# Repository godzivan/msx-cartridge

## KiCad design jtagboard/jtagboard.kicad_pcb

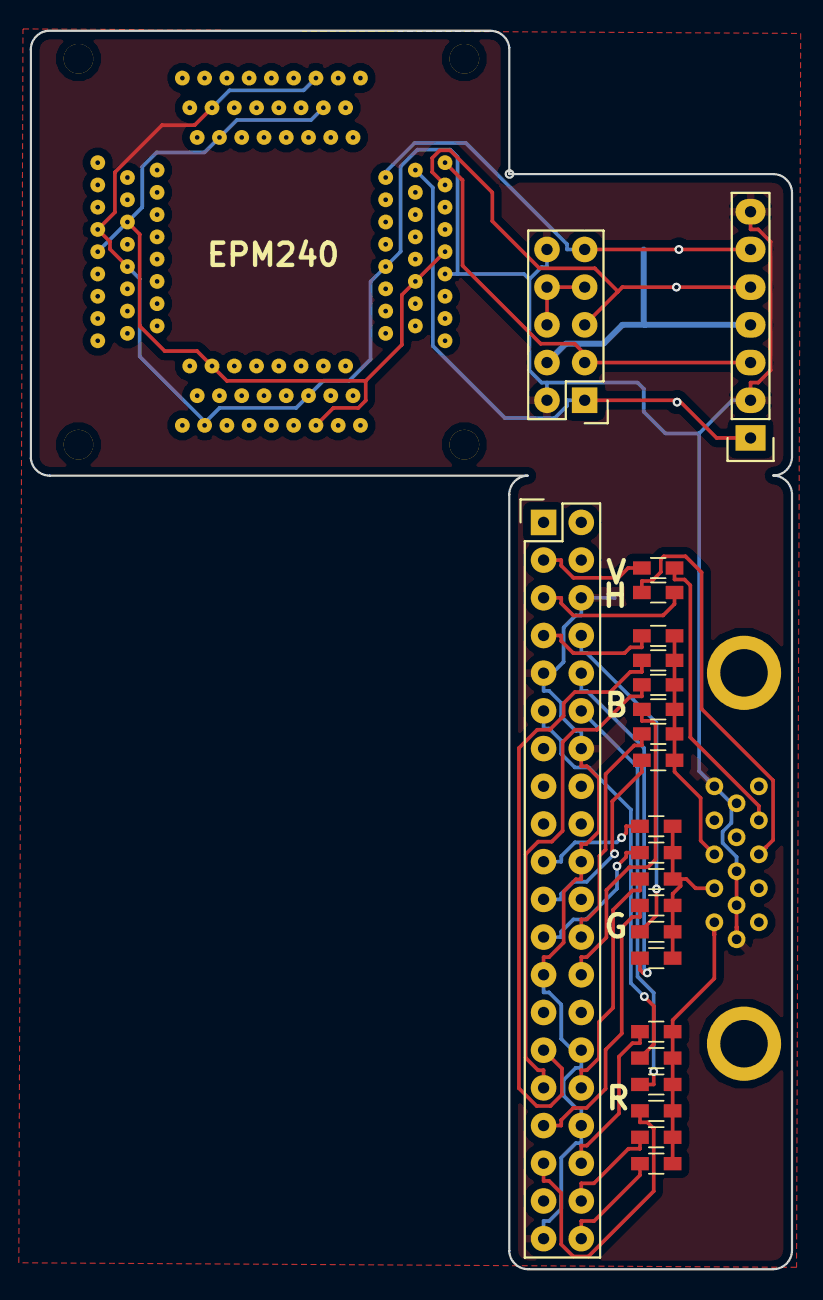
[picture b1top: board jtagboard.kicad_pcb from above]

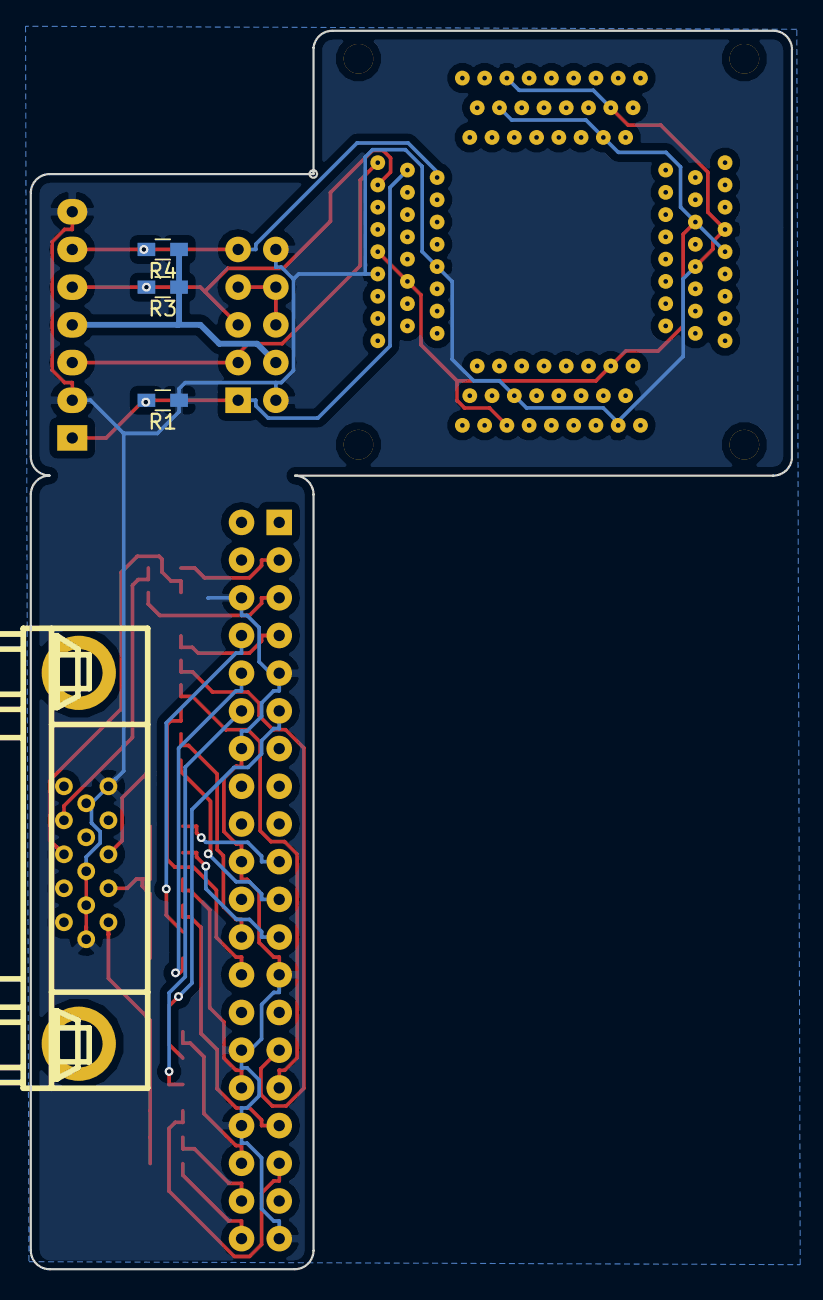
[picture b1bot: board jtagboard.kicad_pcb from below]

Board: 2 copper layers, 51.3 x 83.4 mm, 28 parts (4 on the bottom side), 33 nets.

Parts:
J1: Conn_02x05_Odd_Even; Pin_Header_Straight_2x05
J2: Conn_01x07_Male; Pin_Header_Straight_1x07
J3: DB15_Female_HighDensity; DB_15F-VGA
J4: Raspberry_Pi_2_3; Pin_Header_Straight_2x20
R1, R3, R4, R5, R6, R7, R8, R9, R10, R11, R12, R13, R14, R15, R16, R17, R18, R19, R20, R21, R22, R23, R24: R; R_0603_HandSoldering
U1: MaxII_EPM240; tqfp100

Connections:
/3V3: U1.9, U1.13, U1.31, U1.45, U1.59, U1.63, U1.80, U1.94
/B2: J4.7, R5.2
/B3: J4.29, R6.2
/B4: J4.31, R7.2
/B5: J4.26, R8.2
/B6: J4.24, R9.2
/B7: J4.21, R10.2
/Blue: J3.3, R5.1, R6.1, R7.1, R8.1, R9.1, R10.1
/G2: J4.19, R17.2
/G3: J4.23, R18.2
/G4: J4.32, R19.2
/G5: J4.33, R20.2
/G6: J4.8, R21.2
/G7: J4.10, R22.2
/GND: J1.2, J1.10, J2.2, J2.7, J3.5, J3.6, J3.7, J3.8, J3.10, J4.6, J4.9, J4.14, J4.20, J4.25, J4.30, J4.34, J4.39, R1.1, U1.10, U1.11, U1.32, U1.46, U1.60, U1.65, U1.79, U1.93
/Green: J3.2, R17.1, R18.1, R19.1, R20.1, R21.1, R22.1
/HSync: J3.13, R24.1
/NC: J1.6, J1.7, J1.8
/R2: J4.36, R11.2
/R3: J4.11, R12.2
/R4: J4.12, R13.2
/R5: J4.35, R14.2
/R6: J4.38, R15.2
/R7: J4.40, R16.2
/Red: J3.1, R11.1, R12.1, R13.1, R14.1, R15.1, R16.1
/TCK: J1.1, J2.1, R1.2, U1.24
/TDI: J1.9, J2.6, R4.2, U1.23
/TDO: J1.3, J2.3, U1.25
/TMS: J1.5, J2.5, R3.2, U1.22
/VCC(TRGT): J1.4, J2.4, R3.1, R4.1
/VSync: J3.14, R23.1
/piHSYNC: J4.5, R24.2
/piVSYNC: J4.3, R23.2

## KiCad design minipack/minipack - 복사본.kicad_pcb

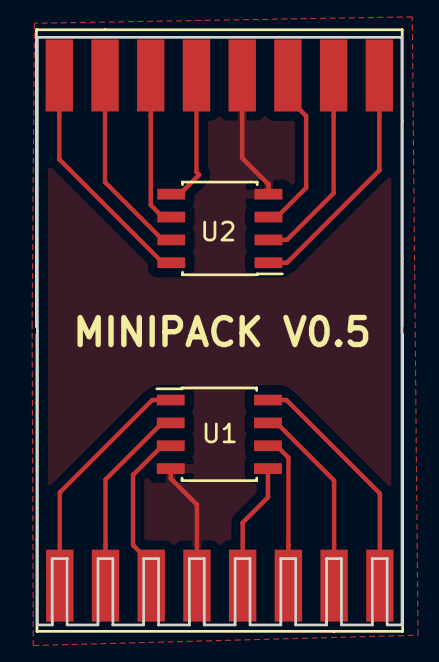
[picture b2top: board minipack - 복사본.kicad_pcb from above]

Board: 2 copper layers, 20.3 x 32.6 mm, 4 parts (0 on the bottom side), 15 nets.

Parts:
J1, J2: Conn_01x08; minipack
U1, U2: W25Q16BVSSIG; SOIC-8_3.9x4.9mm_Pitch1.27mm

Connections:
/CLK: J1.6, U1.6
/CLK2: J2.6, U2.6
/CS: J1.1, U1.1
/CS2: J2.1, U2.1
/GND: J1.4, J2.4, U1.4, U2.4
/HOLD: J1.7, U1.7
/HOLD2: J2.7, U2.7
/MISO: J1.2, U1.2
/MISO2: J2.2, U2.2
/MOSI: J1.5, U1.5
/MOSI2: J2.5, U2.5
/VCC: J1.8, U1.8
/VCC2: J2.8, U2.8
/WP: J1.3, U1.3
/WP2: J2.3, U2.3

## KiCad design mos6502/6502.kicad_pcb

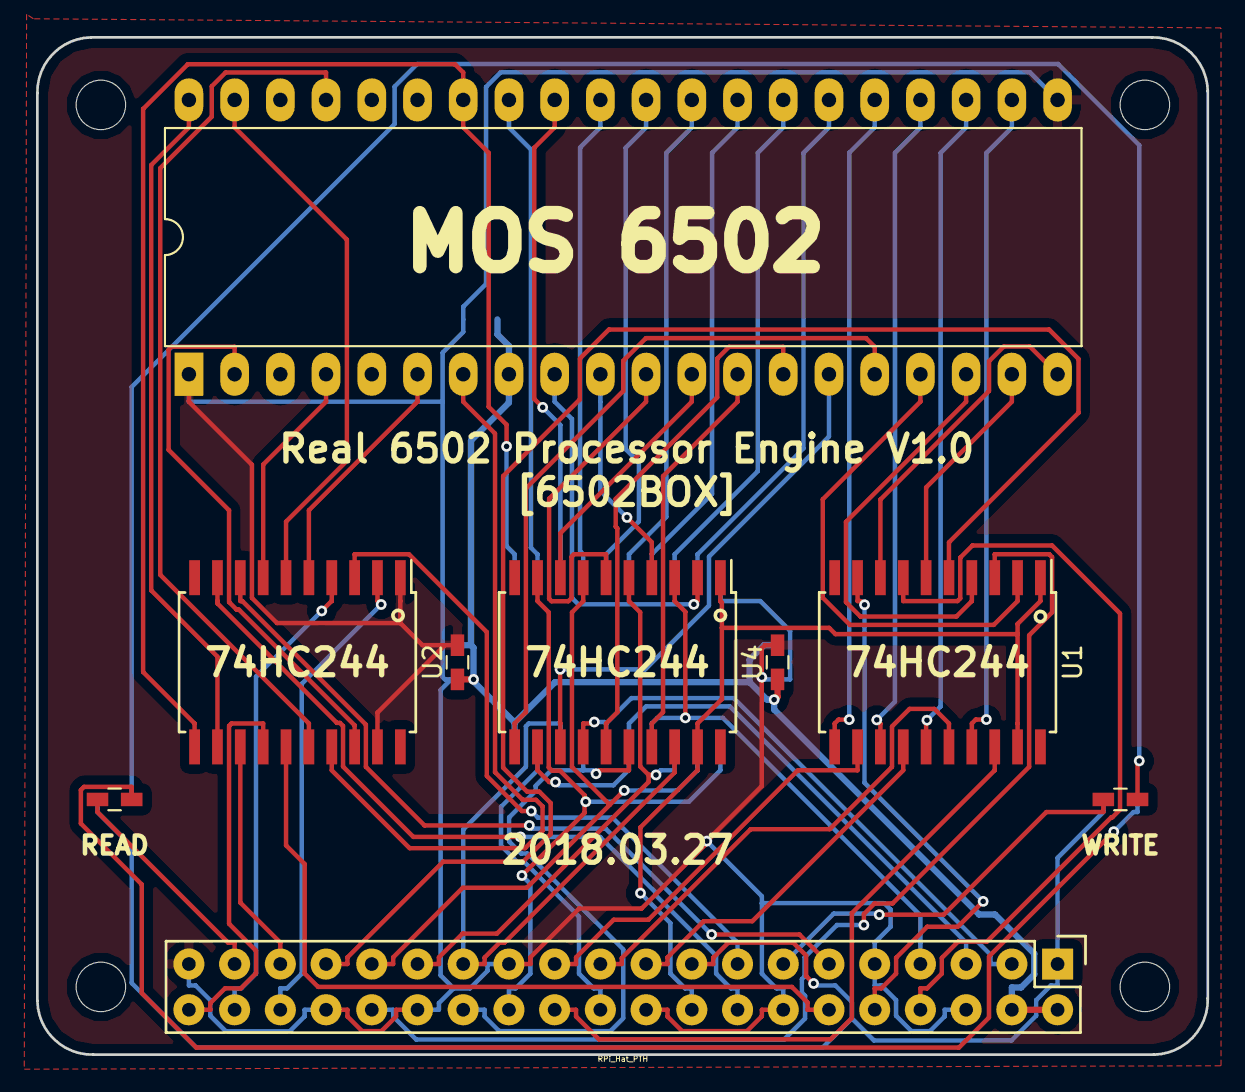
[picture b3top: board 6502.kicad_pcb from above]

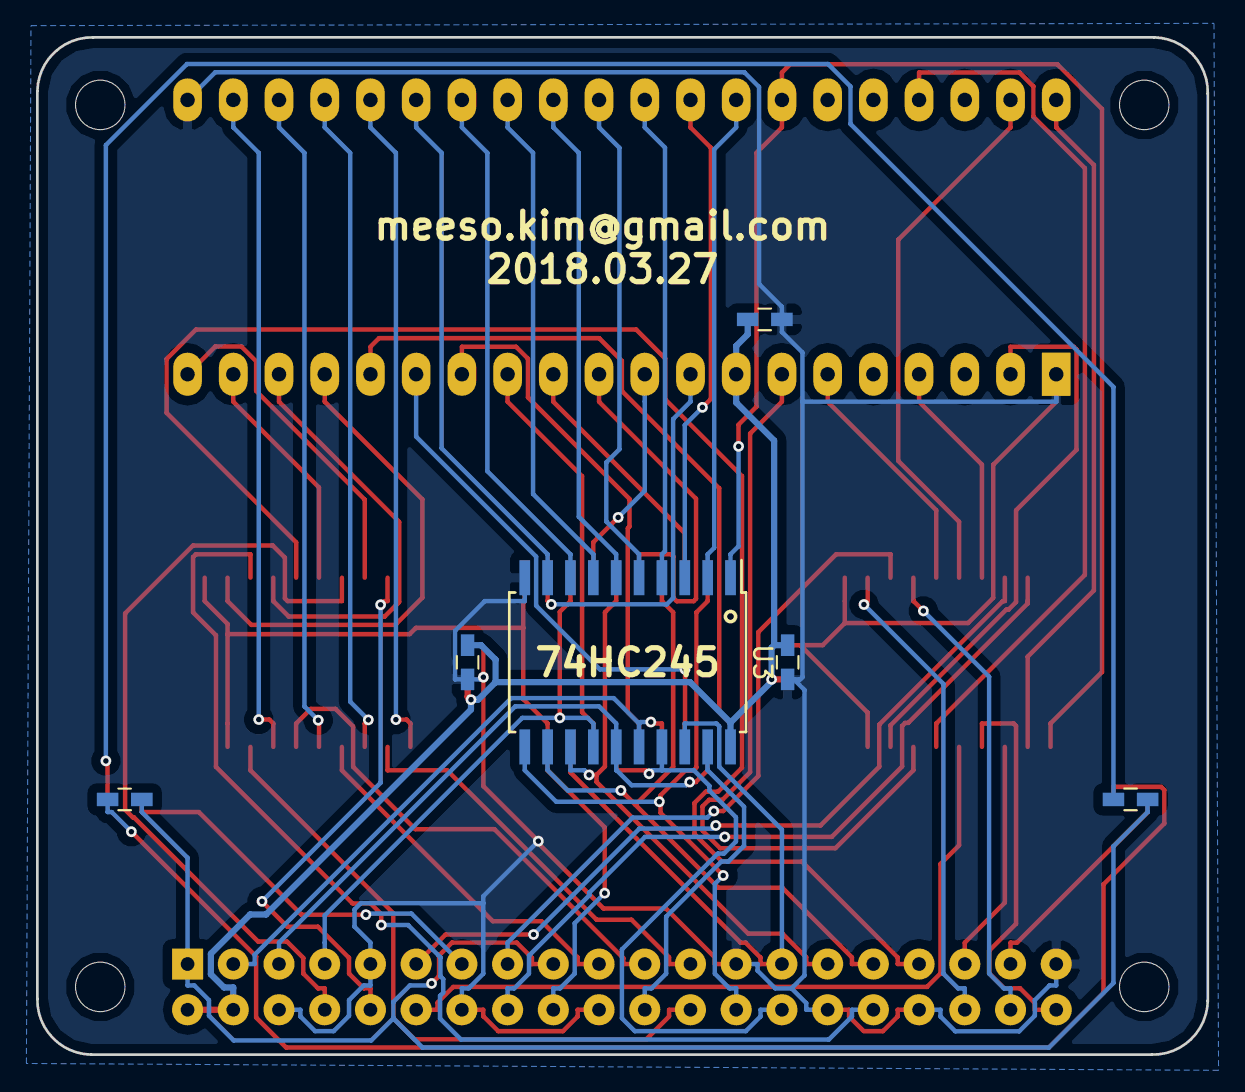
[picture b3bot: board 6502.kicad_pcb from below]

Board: 2 copper layers, 65.0 x 56.5 mm, 15 parts (6 on the bottom side), 65 nets.

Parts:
C1, C2, C3, C4, C5: C; C_0603_HandSoldering
D1, D2: LED; C_0603_HandSoldering
J1: Raspberry_Pi_2_3; Pin_Header_Straight_2x20
R1, R2: R; C_0603_HandSoldering
U1, U2, U4: 74HC244; SOIC-20W_7.5x12.8mm_Pitch1.27mm
U3: 74HC245; SOIC-20W_7.5x12.8mm_Pitch1.27mm
U5: WD65C02; DIP-40_W15.24mm_LongPads

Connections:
/3V3: J1.1, J1.17, R1.1, R2.1
/A0: U4.2, U5.9
/A1: U4.4, U5.10
/A2: U4.6, U5.11
/A3: U4.8, U5.12
/A4: U4.17, U5.13
/A5: U4.15, U5.14
/A6: U4.13, U5.15
/A7: U4.11, U5.16
/A8: U1.2, U5.17
/A9: U1.4, U5.18
/A10: U1.6, U5.19
/A11: U1.8, U5.20
/A12: U1.17, U5.22
/A13: U1.15, U5.23
/A14: U1.13, U5.24
/A15: U1.11, U5.25
/D0: U3.2, U5.33
/D1: U3.3, U5.32
/D2: U3.4, U5.31
/D3: U3.5, U5.30
/D4: U3.6, U5.29
/D5: U3.7, U5.28
/D6: U3.8, U5.27
/D7: U3.9, U5.26
/IRQ: U2.7, U5.4
/NMI: U2.5, U5.6
/PHI0: U2.16, U5.37
/PHI2o: U2.6, U5.39
/RA8: J1.24, U1.18
/RA9: J1.21, U1.16
/RA10: J1.19, U1.14
/RA11: J1.23, U1.12
/RA12: J1.32, U1.3
/RA13: J1.33, U1.5
/RA14: J1.8, U1.7
/RA15: J1.10, U1.9
/RC16: J1.36, U2.2
/RC17: J1.11, U2.8
/RC18: J1.12, U2.15
/RC19: J1.35, U2.13
/RC20: J1.38, U2.4
/RC21: J1.40, U2.14
/RC22: J1.15, U2.3
/RC23: J1.16, U2.9
/RC24: J1.18, U1.1, U1.19, U4.1, U4.19
/RC25: J1.22, U3.19
/RC26: D1.1, J1.37
/RC27: D2.1, J1.13
/RD0: J1.27, U3.18, U4.18
/RD1: J1.28, U3.17, U4.16
/RD2: J1.3, U3.16, U4.14
/RD3: J1.5, U3.15, U4.12
/RD4: J1.7, U3.14, U4.3
/RD5: J1.29, U3.13, U4.5
/RD6: J1.31, U3.12, U4.7
/RD7: J1.26, U3.11, U4.9
/RDY: U2.18, U5.2
/RESET: U2.12, U5.40
/RW: U2.11, U3.1, U5.34
/SYNC: U2.17, U5.7
GND: C1.2, C2.2, C3.2, C4.2, C5.2, J1.6, J1.9, J1.14, J1.20, J1.25, J1.30, J1.34, J1.39, U2.1, U2.19, U3.10, U5.1, U5.21
unnamed: D1.2, R1.2
unnamed: D2.2, R2.2
VCC: C1.1, C2.1, C3.1, C4.1, C5.1, J1.2, J1.4, U3.20, U5.8

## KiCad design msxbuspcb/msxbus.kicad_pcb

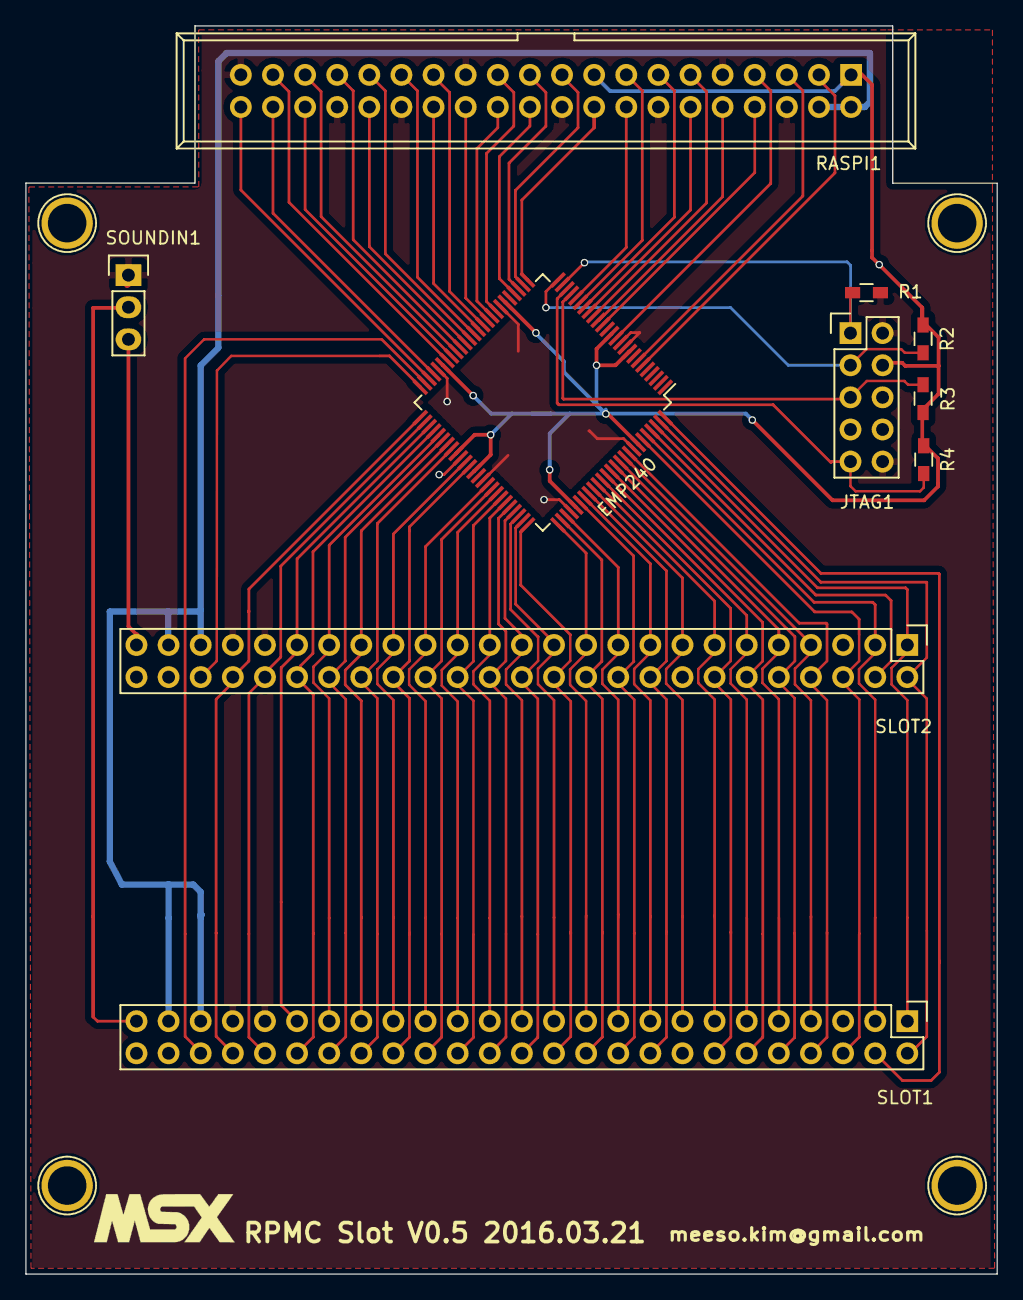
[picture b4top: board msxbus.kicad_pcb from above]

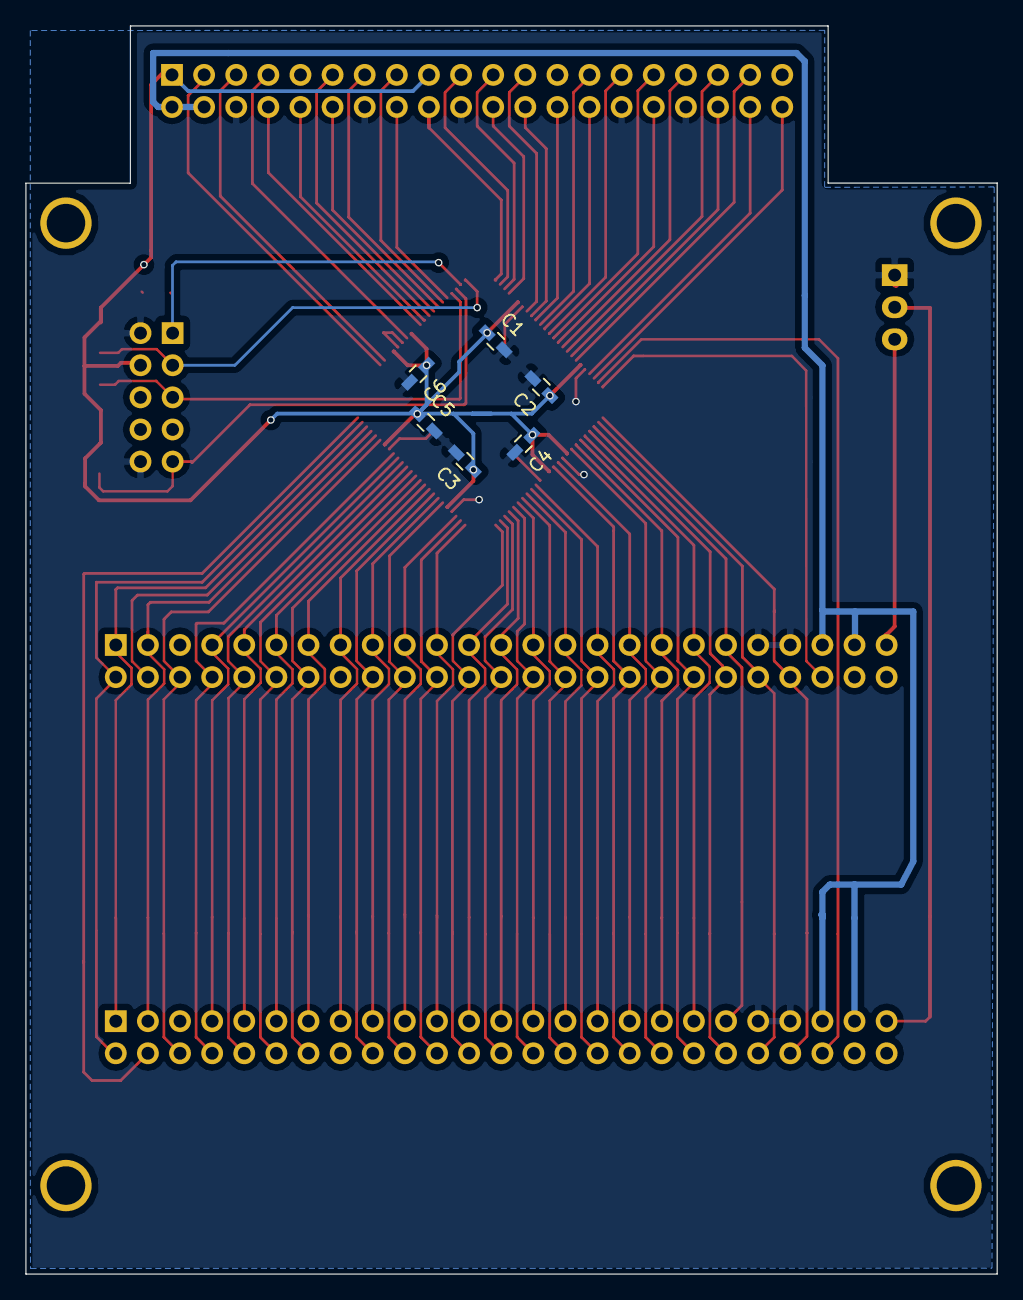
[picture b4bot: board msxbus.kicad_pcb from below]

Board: 2 copper layers, 76.8 x 98.7 mm, 16 parts (6 on the bottom side), 80 nets.

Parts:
C1, C2, C3, C4, C5, C6: C; C_0603_HandSoldering
EMP240: EMP240; TQFP-100_14x14mm_Pitch0.5mm
JTAG1: CONN_02X05; Pin_Header_Straight_2x05
R1, R2, R3, R4: 10K; R_0603_HandSoldering
RASPI1: RPi_GPIO; IDC_Header_Straight_40pins
SLOT1, SLOT2: CONN_02X25; Pin_Header_Straight_2x25
SOUNDIN1: CONN_01X03; Pin_Header_Straight_1x03

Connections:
+3V3: C1.1, C2.1, C3.1, C4.1, C5.1, C6.1, EMP240.9, EMP240.13, EMP240.31, EMP240.45, EMP240.59, EMP240.63, EMP240.80, EMP240.94, JTAG1.4, R2.1, R3.1, R4.1, RASPI1.1, RASPI1.17
+5V: RASPI1.2, RASPI1.4, SLOT1.45, SLOT1.47, SLOT2.45, SLOT2.47
/A0: EMP240.71, SLOT1.28, SLOT2.28
/A1: EMP240.70, SLOT1.27, SLOT2.27
/A2: EMP240.69, SLOT1.30, SLOT2.30
/A3: EMP240.68, SLOT1.29, SLOT2.29
/A4: EMP240.67, SLOT1.32, SLOT2.32
/A5: EMP240.66, SLOT1.31, SLOT2.31
/A6: EMP240.77, SLOT1.22, SLOT2.22
/A7: EMP240.76, SLOT1.21, SLOT2.21
/A8: EMP240.75, SLOT1.24, SLOT2.24
/A9: EMP240.82, SLOT1.17, SLOT2.17
/A10: EMP240.81, SLOT1.20, SLOT2.20
/A11: EMP240.78, SLOT1.19, SLOT2.19
/A12: EMP240.74, SLOT1.23, SLOT2.23
/A13: EMP240.73, SLOT1.26, SLOT2.26
/A14: EMP240.72, SLOT1.25, SLOT2.25
/A15: EMP240.83, SLOT1.18, SLOT2.18
/BUSDIR: EMP240.90, SLOT1.10, SLOT2.10
/CLOCK: EMP240.52, SLOT1.42, SLOT2.42
/CS1: EMP240.98, SLOT1.1, SLOT2.1
/CS2: EMP240.99, SLOT1.2, SLOT2.2
/CS12: EMP240.96, SLOT1.3, SLOT2.3
/D0: EMP240.62, SLOT1.34, SLOT2.34
/D1: EMP240.61, SLOT1.33, SLOT2.33
/D2: EMP240.58, SLOT1.36, SLOT2.36
/D3: EMP240.57, SLOT1.35, SLOT2.35
/D4: EMP240.56, SLOT1.38, SLOT2.38
/D5: EMP240.55, SLOT1.37, SLOT2.37
/D6: EMP240.54, SLOT1.40, SLOT2.40
/D7: EMP240.53, SLOT1.39, SLOT2.39
/INT: EMP240.92, SLOT1.8, SLOT2.8
/IORQ: EMP240.87, SLOT1.11, SLOT2.11
/M1: EMP240.89, SLOT1.9, SLOT2.9
/MA0: EMP240.26, RASPI1.18
/MCS: EMP240.44, RASPI1.37
/MD00: EMP240.36, RASPI1.27
/MD01: EMP240.37, RASPI1.28
/MD02: EMP240.6, RASPI1.3
/MD03: EMP240.7, RASPI1.5
/MD04: EMP240.12, RASPI1.7
/MD05: EMP240.38, RASPI1.29
/MD06: EMP240.39, RASPI1.31
/MD07: EMP240.35, RASPI1.26
/MD08: EMP240.34, RASPI1.24
/MD09: EMP240.28, RASPI1.21
/MD10: EMP240.27, RASPI1.19
/MD11: EMP240.33, RASPI1.23
/MD12: EMP240.40, RASPI1.32
/MD13: EMP240.41, RASPI1.33
/MD14: EMP240.15, RASPI1.8
/MD15: EMP240.16, RASPI1.10
/MERQ: EMP240.88, SLOT1.12, SLOT2.12
/MEXT: EMP240.19, RASPI1.13
/MIORQ: EMP240.42, RASPI1.35
/MMERQ: EMP240.18, RASPI1.12
/MODE: EMP240.29, RASPI1.22
/MRD: EMP240.17, RASPI1.11
/MRESET: EMP240.47, RASPI1.38
/MSLTSL0: EMP240.48, RASPI1.40
/MSLTSL1: EMP240.20, RASPI1.15
/MWAIT: EMP240.21, RASPI1.16
/MWR: EMP240.43, RASPI1.36
/NWAIT: EMP240.91, SLOT1.7, SLOT2.7
/RD: EMP240.86, SLOT1.14, SLOT2.14
/RESET: EMP240.84, SLOT1.15, SLOT2.15
/RFSH: EMP240.95, SLOT1.6, SLOT2.6
/SLTSL0: EMP240.97, SLOT2.4
/SLTSL1: EMP240.100, SLOT1.4
/SOUNDIN0: SLOT1.49, SOUNDIN1.2
/SOUNDIN1: SLOT2.49, SOUNDIN1.3
/SW1: EMP240.50, SLOT2.46
/SW2: EMP240.49, SLOT1.46
/SWOUT: EMP240.51, SLOT1.44, SLOT2.44
/TCK: EMP240.24, JTAG1.1, R1.2
/TDI: EMP240.23, JTAG1.9, R4.2
/TDO: EMP240.25, JTAG1.3, R2.2
/TMS: EMP240.22, JTAG1.5, R3.2
/WR: EMP240.85, SLOT1.13, SLOT2.13
GND: C1.2, C2.2, C3.2, C4.2, C5.2, C6.2, EMP240.10, EMP240.11, EMP240.32, EMP240.46, EMP240.60, EMP240.65, EMP240.79, EMP240.93, JTAG1.2, JTAG1.10, R1.1, RASPI1.6, RASPI1.9, RASPI1.14, RASPI1.20, RASPI1.25, RASPI1.30, RASPI1.34, RASPI1.39, SLOT1.41, SLOT1.43, SLOT2.41, SLOT2.43, SOUNDIN1.1

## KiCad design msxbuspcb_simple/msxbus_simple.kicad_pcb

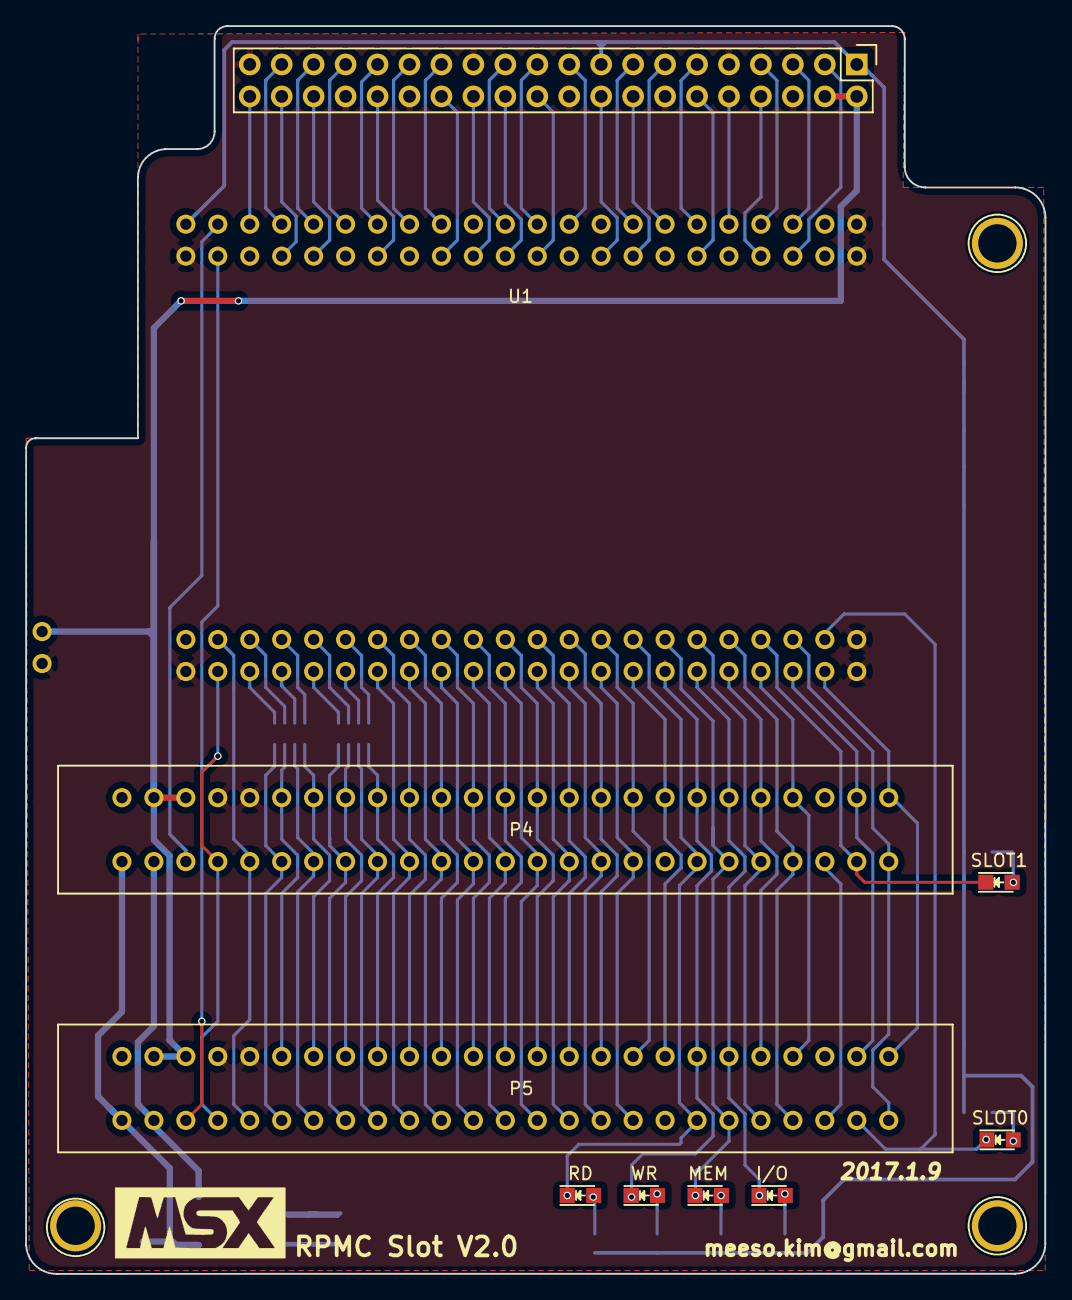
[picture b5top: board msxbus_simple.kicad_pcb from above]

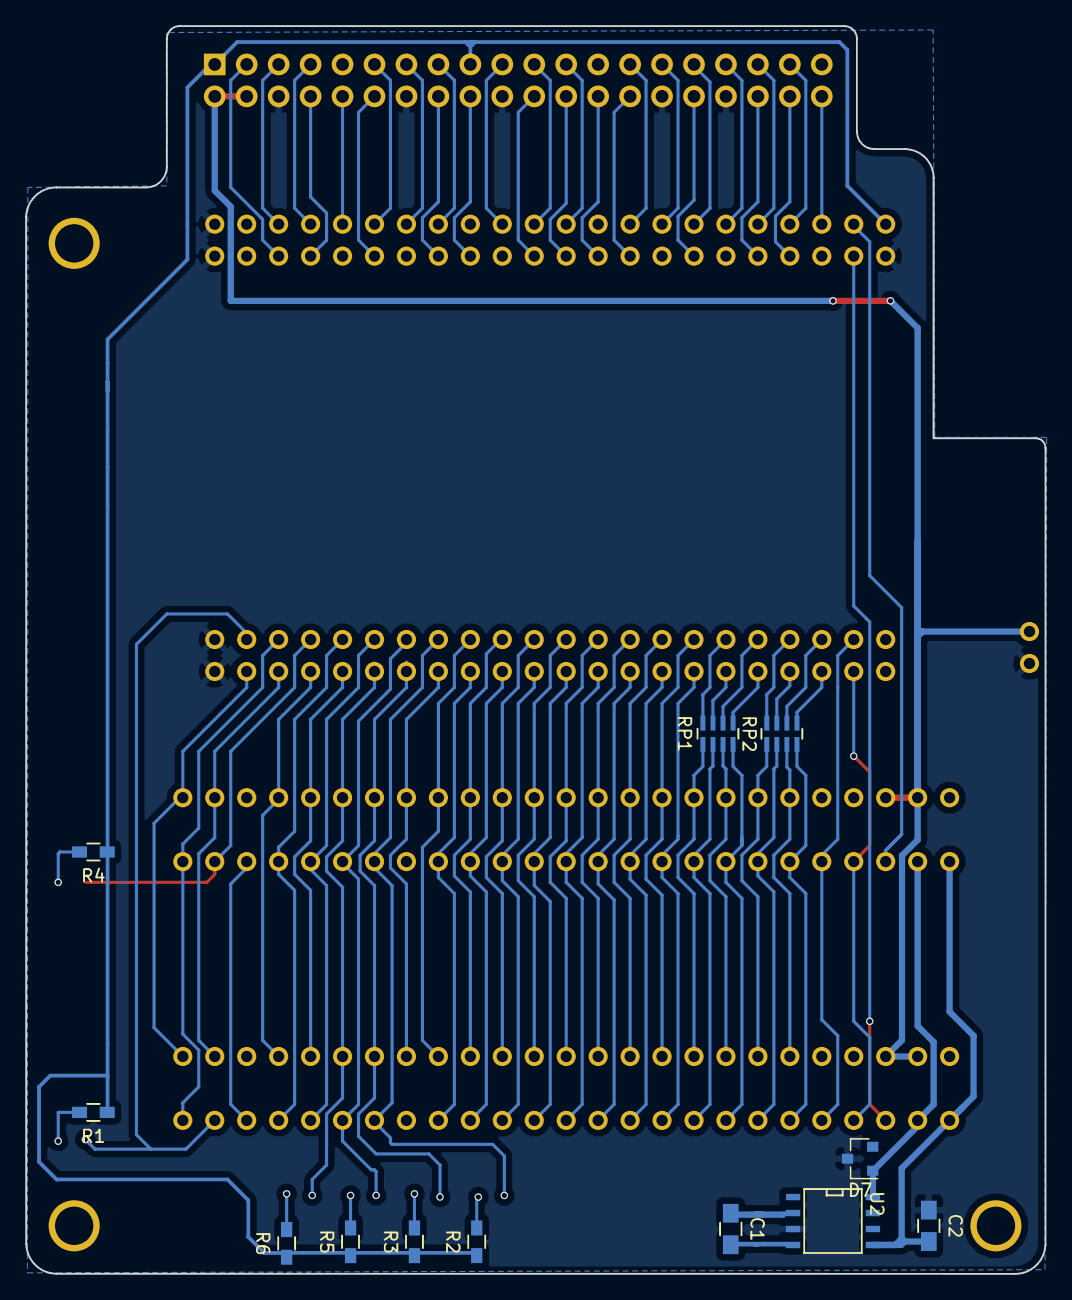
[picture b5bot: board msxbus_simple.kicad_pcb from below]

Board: 2 copper layers, 81.0 x 99.2 mm, 22 parts (12 on the bottom side), 92 nets.

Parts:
C1, C2: CP1; C_0805_HandSoldering
D7: D_Schottky_x2_Serial_AKC; SOT-23
I/O: LED; LED_0805
J1: RPi_GPIO; Pin_Header_Straight_2x20
MEM: LED; LED_0805
P4, P5: CONN_02X25; MSX_SLOT
R1, R2, R3, R4, R5, R6: R; R_0603_HandSoldering
RD: LED; LED_0805
RP1, RP2: R_PACK4; R_Array_Concave_4x0603
SLOT0, SLOT1: LED; LED_0805
U1: CPLD; emp270_board
U2: ICL7660A; SOIC-8-N
WR: LED; LED_0805

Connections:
+3V3: J1.1, J1.17, R1.1, R2.1, R3.1, R4.1, R5.1, R6.1, U1.43, U1.46
+5V: J1.2, J1.4, P4.45, P4.47, P5.45, P5.47, U1.89
+12V: D7.1, P4.48, P5.48, U2.8
/-12V: C2.2, P4.50, P5.50, U2.5
/A0: P4.28, P5.28, U1.61
/A1: P4.27, P5.27, U1.62
/A2: P4.30, P5.30, U1.59
/A3: P4.29, P5.29, U1.60
/A4: P4.32, P5.32, U1.57
/A5: P4.31, P5.31, U1.58
/A6: P4.22, P5.22, U1.67
/A7: P4.21, P5.21, U1.68
/A8: P4.24, P5.24, U1.65
/A9: P4.17, P5.17, U1.72
/A10: P4.20, P5.20, U1.69
/A11: P4.19, P5.19, U1.70
/A12: P4.23, P5.23, U1.66
/A13: P4.26, P5.26, U1.63
/A14: P4.25, P5.25, U1.64
/A15: P4.18, P5.18, U1.71
/BUSDIR: P4.10, P5.10, U1.78
/C+: C1.1, U2.2
/C-: C1.2, U2.4
/CLOCK: P4.42, P5.42, U1.48
/CS1: P4.1, P5.1, U1.85
/CS2: P4.2, P5.2, U1.84
/CS12: P4.3, P5.3, U1.83
/D0: P4.34, P5.34, RP1.2
/D1: P4.33, P5.33, RP1.1
/D2: P4.36, P5.36, RP1.4
/D3: P4.35, P5.35, RP1.3
/D4: P4.38, P5.38, RP2.2
/D5: P4.37, P5.37, RP2.1
/D6: P4.40, P5.40, RP2.4
/D7: P4.39, P5.39, RP2.3
/INT: P4.8, P5.8, U1.80
/IORQ: I/O.1, P4.11, P5.11, U1.77
/M1: P4.9, P5.9, U1.79
/MA0: J1.18, U1.18
/MCS: J1.37, U1.37
/MD00: J1.27, U1.27
/MD01: J1.28, U1.28
/MD02: J1.3, U1.6
/MD03: J1.5, U1.5
/MD04: J1.7, U1.7
/MD05: J1.29, U1.29
/MD06: J1.31, U1.31
/MD07: J1.26, U1.26
/MD08: J1.24, U1.24
/MD09: J1.21, U1.21
/MD10: J1.19, U1.19
/MD11: J1.23, U1.23
/MD12: J1.32, U1.32
/MD13: J1.33, U1.33
/MD14: J1.8, U1.8
/MD15: J1.10, U1.9
/MERQ: MEM.1, P4.12, P5.12, U1.76
/MEXT: J1.13, U1.13
/MIORQ: J1.35, U1.35
/MMERQ: J1.12, U1.12
/MODE: J1.22, U1.22
/MRD: J1.11, U1.11
/MRESET: J1.38, U1.38
/MSLTSL0: J1.40, U1.39
/MSLTSL1: J1.15, U1.15
/MWAIT: J1.16, U1.16
/MWR: J1.36, U1.36
/NWAIT: P4.7, P5.7, U1.81
/RD: P4.14, P5.14, RD.1, U1.74
/RD0: RP1.7, U1.55
/RD1: RP1.8, U1.56
/RD2: RP1.5, U1.53
/RD3: RP1.6, U1.54
/RD4: RP2.7, U1.51
/RD5: RP2.8, U1.52
/RD6: RP2.5, U1.49
/RD7: RP2.6, U1.50
/RESET: P4.15, P5.15, U1.73
/RFSH: P4.6, P5.6
/SLTSL0: P4.4, SLOT1.1, U1.82
/SLTSL1: P5.4, SLOT0.1, U1.86
/SW1: P4.46, U1.41
/SW2: P5.46, U1.42
/SWOUT: P4.44, P5.44, U1.47
/WR: P4.13, P5.13, U1.75, WR.1
GND: C2.1, D7.3, J1.6, J1.9, J1.14, J1.20, J1.25, J1.30, J1.34, J1.39, P4.41, P4.43, P5.41, P5.43, U1.1, U1.2, U1.44, U1.45, U1.87, U1.88, U1.90, U2.3
unnamed: I/O.2, R6.2
unnamed: MEM.2, R5.2
unnamed: R1.2, SLOT0.2
unnamed: R2.2, RD.2
unnamed: R3.2, WR.2
unnamed: R4.2, SLOT1.2

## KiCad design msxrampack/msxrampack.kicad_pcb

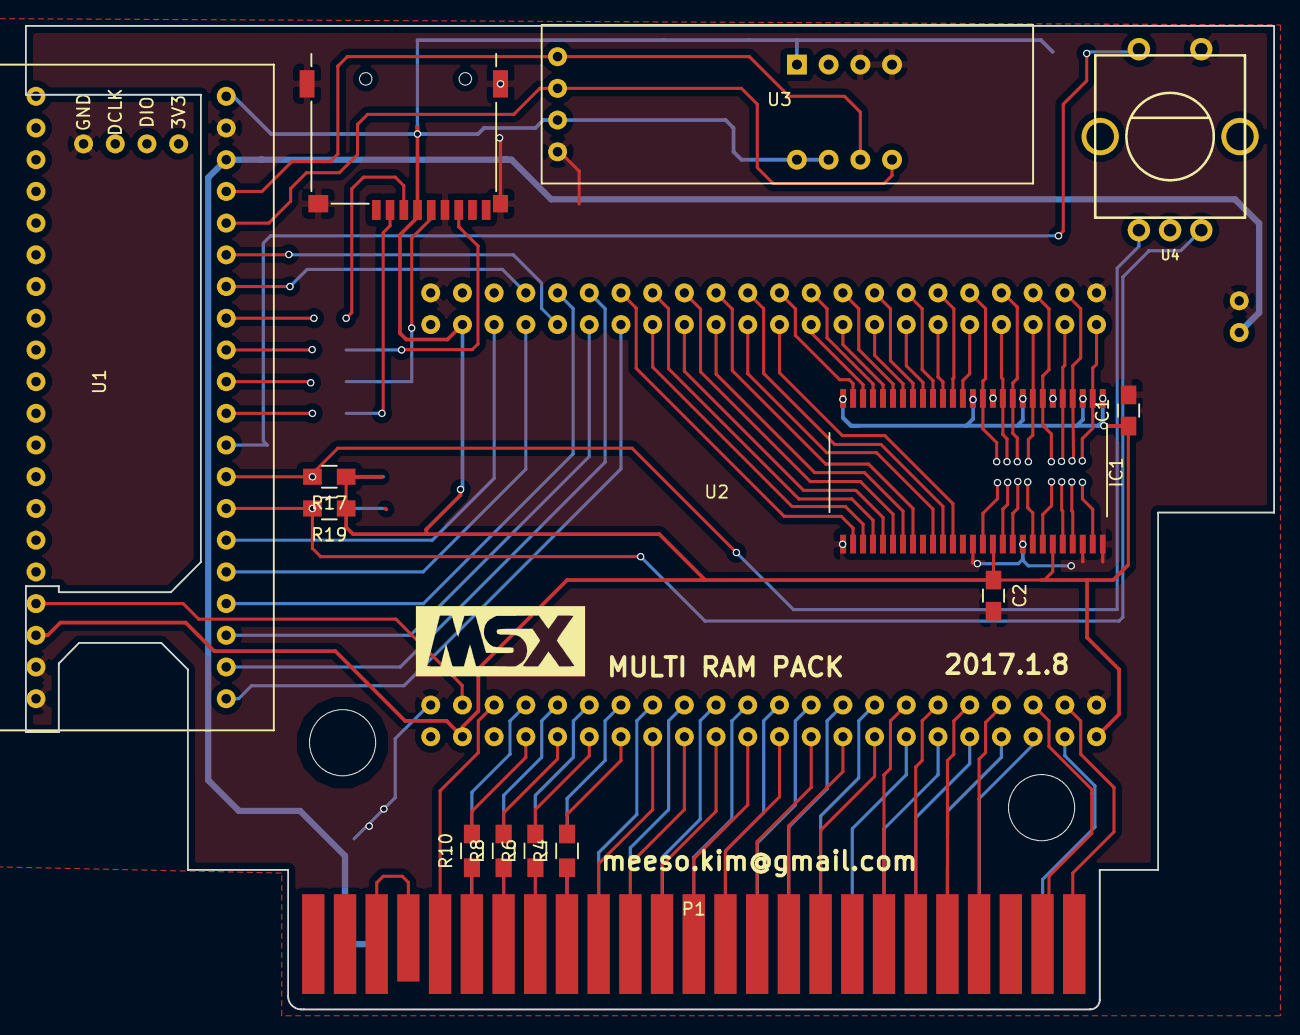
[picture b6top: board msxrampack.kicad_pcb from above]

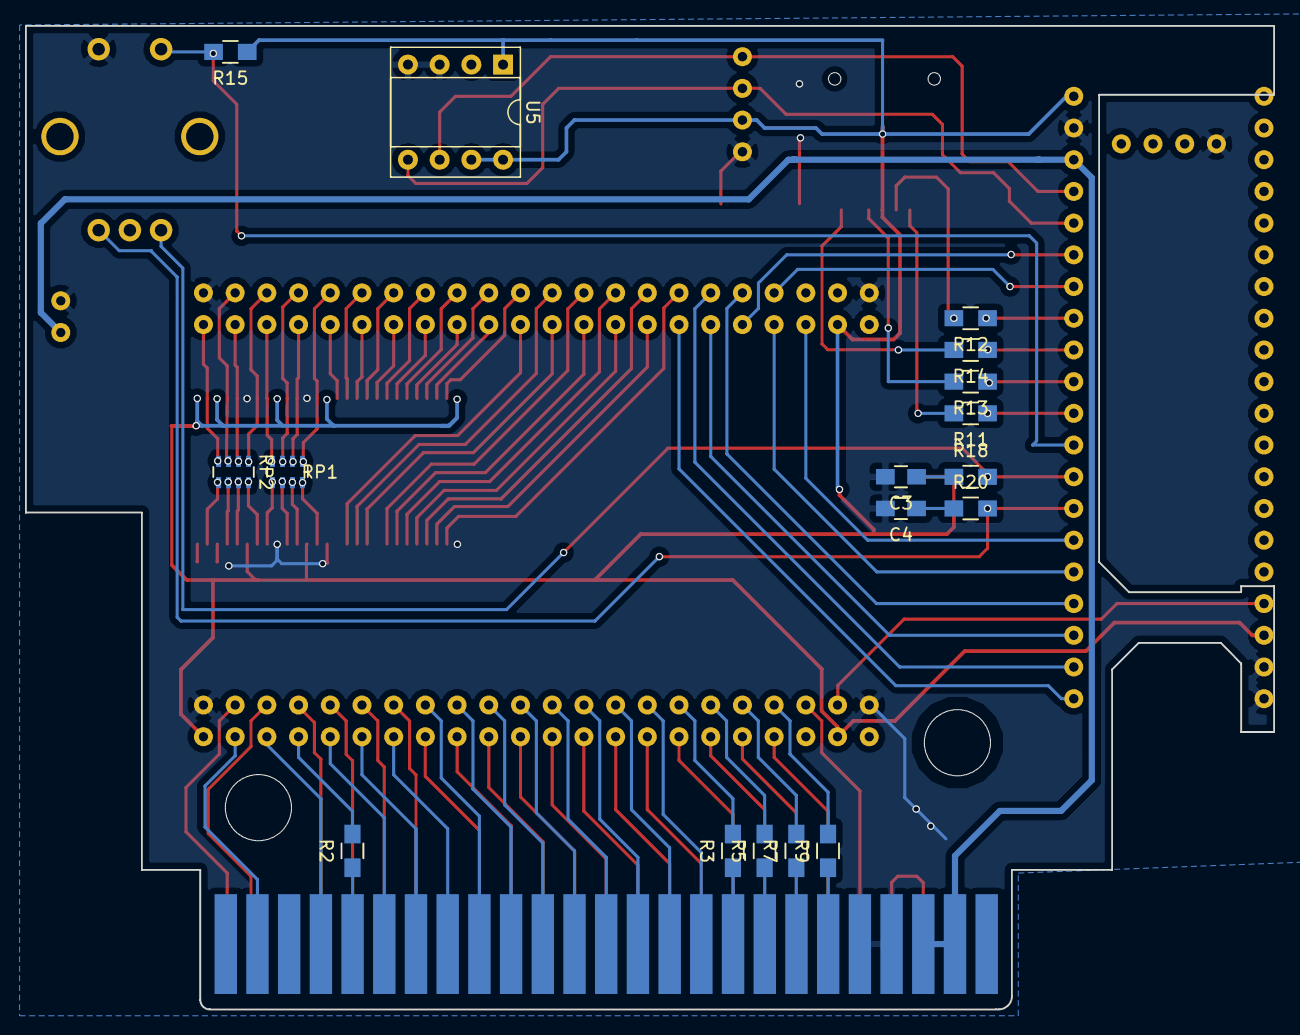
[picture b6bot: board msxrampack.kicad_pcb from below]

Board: 2 copper layers, 100.0 x 78.8 mm, 32 parts (17 on the bottom side), 112 nets.

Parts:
C1, C2, C3, C4: C_Small; C_0805_HandSoldering
IC1: MT48LC4M16A2TG; TSOP-II_54_11.7x22.3mm_Pitch0.8mm
J1: MicroSD; Conn_uSDcard
P1: MSX_SLOT; card_edge_connector
R2, R3, R4, R5, R6, R7, R8, R9, R10, R11, R12, R13, R14, R15, R17, R18, R19, R20: R; R_0805_HandSoldering
RP1, RP2: R_PACK4; R_Array_Concave_4x0603_Handsoldering
U1: STM32F103
U2: CPLD; emp270_board
U3: OLED128x32
U4: RotaryEncoder; SF-ROTARY-ENCODER
U5: 24C512; DIP-8_W7.62mm_Socket

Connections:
+3V3: C1.1, C2.1, IC1.1, IC1.3, IC1.9, IC1.14, IC1.27, IC1.43, IC1.49, J1.4, R15.1, R17.1, R19.1, U1.20, U1.38, U2.3, U2.43, U2.86, U3.3, U5.1, U5.7, U5.8
+5V: P1.45, P1.47, U1.18, U2.89
/A0: P1.28, U2.19
/A1: P1.27, U2.20
/A2: P1.30, U2.17
/A3: P1.29, U2.18
/A4: P1.32, U2.15
/A5: P1.31, U2.16
/A6: P1.22, U2.25
/A7: P1.21, U2.26
/A8: P1.24, U2.23
/A9: P1.17, U2.30
/A10: P1.20, U2.27
/A11: P1.19, U2.28
/A12: P1.23, U2.24
/A13: P1.26, U2.21
/A14: P1.25, U2.22
/A15: P1.18, U2.29
/BA0: IC1.20, U2.59
/BA1: IC1.21, U2.60
/BUSDIR: P1.10, U2.36
/CAS: IC1.17, U2.56
/CKE: IC1.37, U2.68
/CLK: IC1.38, U2.67
/CLOCK: P1.42, U2.6
/CS: IC1.19, U2.58
/CS2: P1.2, U2.42
/CS12: P1.3, U2.41
/CS_RAM: U1.1, U2.76
/CS_SD: R11.1, U1.10
/CS_SD_: J1.2, R11.2
/D0: P1.34, R4.1
/D1: P1.33, R3.1
/D2: P1.36, R6.1
/D3: P1.35, R5.1
/D4: P1.38, R8.1
/D5: P1.37, R7.1
/D6: P1.40, R10.1
/D7: P1.39, R9.1
/DQ0: IC1.2, RP2.4, U2.46
/DQ1: IC1.4, RP2.3, U2.47
/DQ2: IC1.5, RP2.2, U2.48
/DQ3: IC1.7, RP2.1, U2.49
/DQ4: IC1.8, RP1.4, U2.50
/DQ5: IC1.10, RP1.3, U2.51
/DQ6: IC1.11, RP1.2, U2.52
/DQ7: IC1.13, RP1.1, U2.53
/DQ8: IC1.42, RP1.8
/DQ9: IC1.44, RP1.7
/DQ10: IC1.45, RP1.6
/DQ11: IC1.47, RP1.5
/DQ12: IC1.48, RP2.8
/DQ13: IC1.50, RP2.7
/DQ14: IC1.51, RP2.6
/DQ15: IC1.53, RP2.5
/DQMH: IC1.39, U2.66
/DQML: IC1.15, U2.54
/EXT0: U1.5, U2.82
/EXT1: U1.6, U2.84
/INT: P1.8, U2.38
/IORQ: P1.11, U2.35
/LDIR: R17.2, R18.2, U1.8, U4.2
/M1: P1.9, R2.1
/MERQ: P1.12, U2.34
/MISO: U1.3, U2.78
/MISO_SD: R14.1, U1.12
/MISO_SD_: J1.7, R14.2
/MOSI: U1.4, U2.79
/MOSI_SD: R12.1, U1.13
/MOSI_SD_: J1.3, R12.2
/RA0: IC1.23, U2.62
/RA1: IC1.24, U2.63
/RA2: IC1.25, U2.64
/RA3: IC1.26, U2.65
/RA4: IC1.29, U2.75
/RA5: IC1.30, U2.74
/RA6: IC1.31, U2.73
/RA7: IC1.32, U2.72
/RA8: IC1.33, U2.71
/RA9: IC1.34, U2.70
/RA10: IC1.22, U2.61
/RA11: IC1.35, U2.69
/RAS: IC1.18, U2.57
/RD: P1.14, U2.32
/RDIR: R19.2, R20.2, U1.7, U4.4
/RESET: P1.15, U2.31
/RST: U1.37, U2.4
/RX: U1.15, U2.80
/SCK: U1.2, U2.77
/SCK_SD: R13.1, U1.11
/SCK_SD_: J1.5, R13.2
/SDA: U1.16, U3.2, U5.5
/SDL: U1.17, U3.1, U5.6
/SLTSL: P1.4, U2.40
/SW: P1.44, P1.46
/SW1: R15.2, U1.9, U4.1
/TX: U1.14, U2.81
/WAIT: P1.7, U2.39
/WE: IC1.16, U2.55
/WR: P1.13, U2.33
/_D0: R4.2, U2.13
/_D1: R3.2, U2.14
/_D2: R6.2, U2.11
/_D3: R5.2, U2.12
/_D4: R8.2, U2.9
/_D5: R7.2, U2.10
/_D6: R10.2, U2.7
/_D7: R9.2, U2.8
/_M1: R2.2, U2.37
GND: C1.2, C2.2, C3.2, C4.2, IC1.6, IC1.12, IC1.28, IC1.41, IC1.46, IC1.52, IC1.54, J1.6, P1.41, P1.43, U1.19, U1.39, U1.40, U1.41, U2.2, U2.44, U2.45, U2.87, U2.90, U3.4, U4.5, U5.3, U5.4
unnamed: C3.1, R18.1
unnamed: C4.1, R20.1
